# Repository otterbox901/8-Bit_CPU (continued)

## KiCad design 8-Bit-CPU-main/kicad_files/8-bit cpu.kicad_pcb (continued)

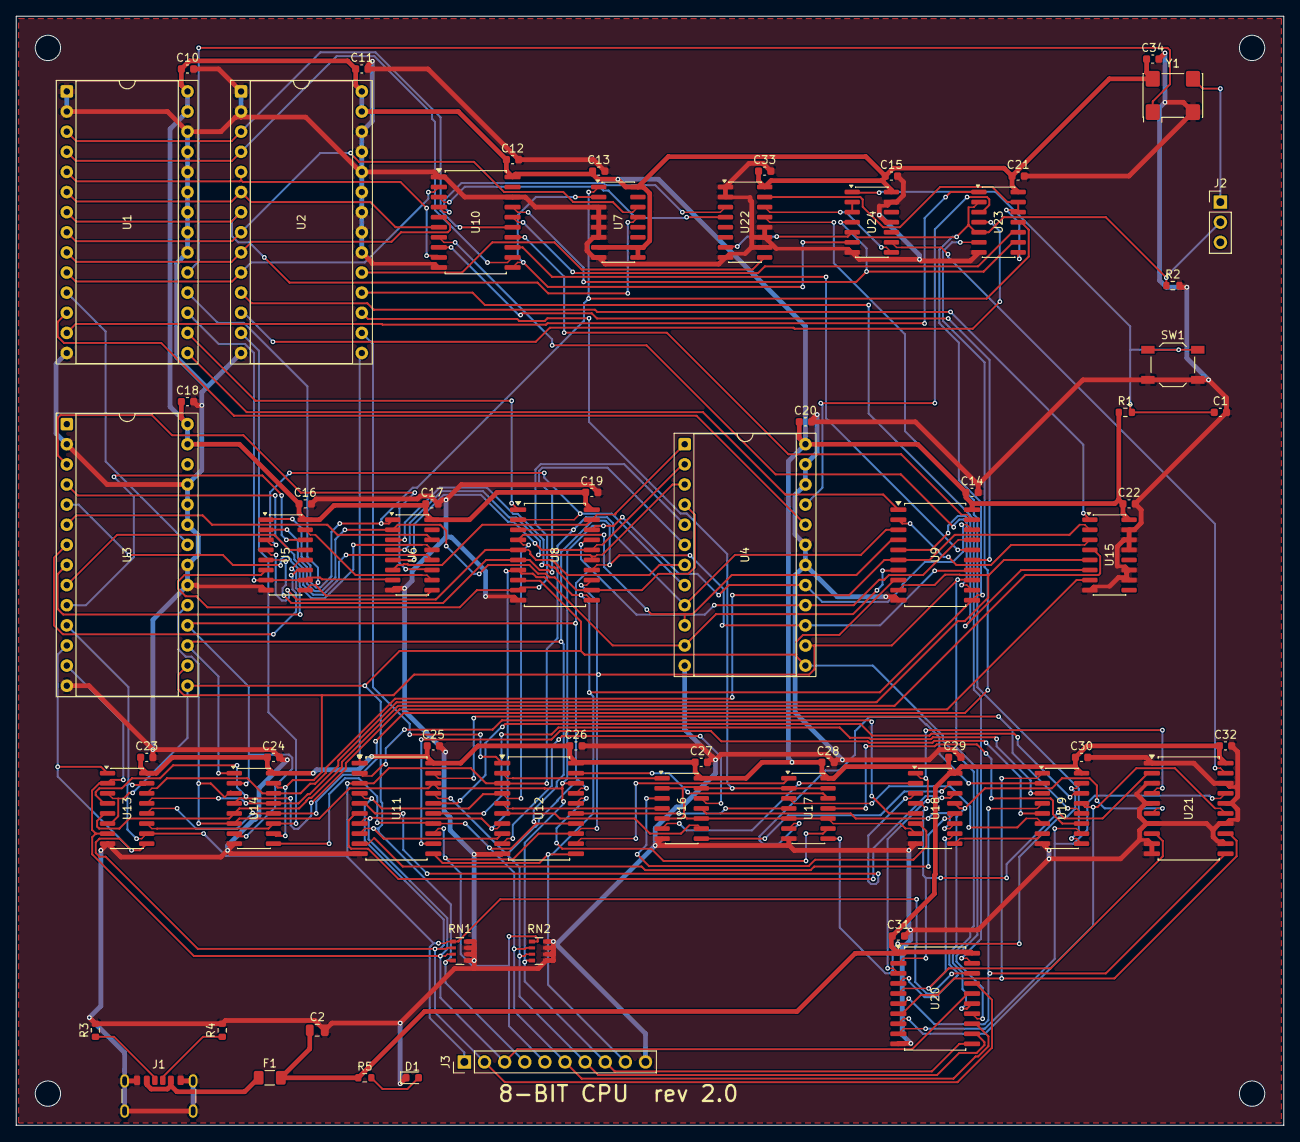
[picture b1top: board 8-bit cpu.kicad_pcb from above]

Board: 2 copper layers, 160.0 x 140.0 mm, 69 parts (0 on the bottom side), 114 nets.

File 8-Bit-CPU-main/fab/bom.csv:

"Reference","Value","Footprint","Qty"
"C1","1uF","Capacitor_SMD:C_0603_1608Metric","1"
"C2","10uF","Capacitor_SMD:C_0805_2012Metric","1"
"C10-C34","100nF","Capacitor_SMD:C_0603_1608Metric","25"
"D1","PWR","LED_SMD:LED_0603_1608Metric","1"
"F1","750mA hold","Fuse:Fuse_1206_3216Metric","1"
"J1","USB-C 5V","Connector_USB:USB_C_Receptacle_GCT_USB4125-xx-x_6P_TopMnt_Horizontal","1"
"J2","CLK SEL","Connector_PinHeader_2.54mm:PinHeader_1x03_P2.54mm_Vertical","1"
"J3","DEBUG","Connector_PinHeader_2.54mm:PinHeader_1x10_P2.54mm_Vertical","1"
"R1,R2","10k","Resistor_SMD:R_0603_1608Metric","2"
"R3,R4","5.1k","Resistor_SMD:R_0603_1608Metric","2"
"R5","1k","Resistor_SMD:R_0603_1608Metric","1"
"RN1,RN2","10k x4","Resistor_SMD:R_Array_Convex_4x0603","2"
"SW1","RESET","Button_Switch_SMD:SW_SPST_TL3342","1"
"U1","AT28C256 (ctrl ROM 1)","Package_DIP:DIP-28_W15.24mm_Socket","1"
"U2","AT28C256 (ctrl ROM 2)","Package_DIP:DIP-28_W15.24mm_Socket","1"
"U3","AT28C64B (program ROM)","Package_DIP:DIP-28_W15.24mm_Socket","1"
"U4","HM6116 (data RAM)","Package_DIP:DIP-24_W15.24mm_Socket","1"
"U5","74HC161 (PC lo)","Package_SO:SOIC-16_3.9x9.9mm_P1.27mm","1"
"U6","74HC161 (PC hi)","Package_SO:SOIC-16_3.9x9.9mm_P1.27mm","1"
"U7","74HC161","Package_SO:SOIC-16_3.9x9.9mm_P1.27mm","1"
"U8","74HC377 (MAR)","Package_SO:SOIC-20W_7.5x12.8mm_P1.27mm","1"
"U9","74HC377 (IR)","Package_SO:SOIC-20W_7.5x12.8mm_P1.27mm","1"
"U10","74HC377","Package_SO:SOIC-20W_7.5x12.8mm_P1.27mm","1"
"U11","74HC377 (A)","Package_SO:SOIC-20W_7.5x12.8mm_P1.27mm","1"
"U12","74HC377 (TEMP)","Package_SO:SOIC-20W_7.5x12.8mm_P1.27mm","1"
"U13","74HC670 (R0-R3 bits 0-3)","Package_SO:SOIC-16_3.9x9.9mm_P1.27mm","1"
"U14","74HC670 (R0-R3 bits 4-7)","Package_SO:SOIC-16_3.9x9.9mm_P1.27mm","1"
"U15","74HC157","Package_SO:SOIC-16_3.9x9.9mm_P1.27mm","1"
"U16,U17","74HC86","Package_SO:SOIC-14_3.9x8.7mm_P1.27mm","2"
"U18,U19","74HC283","Package_SO:SOIC-16_3.9x9.9mm_P1.27mm","2"
"U20","74HC245 (ALU out)","Package_SO:SOIC-20W_7.5x12.8mm_P1.27mm","1"
"U21","74HC688 (zero detect)","Package_SO:SOIC-20W_7.5x12.8mm_P1.27mm","1"
"U22","74HC173 (flags)","Package_SO:SOIC-16_3.9x9.9mm_P1.27mm","1"
"U23","74HC00","Package_SO:SOIC-14_3.9x8.7mm_P1.27mm","1"
"U24","74HC14","Package_SO:SOIC-14_3.9x8.7mm_P1.27mm","1"
"Y1","1MHz osc, tri-state OE","Oscillator:Oscillator_SMD_SeikoEpson_SG8002CA-4Pin_7.0x5.0mm","1"
